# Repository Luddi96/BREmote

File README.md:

# BREmote - Open Source eFoil and Esk8 remote 

## Features:
* All mechanical parts 3D printed (even the springs)
* Symmetric design - left & right side can be swapped
* Sustainable - All external parts can be replaced
* Open Source: 3D Models, Electronics and Software are GPL3.0
* 2.4GHz Link (range dependant on antenna type, position)
* Communication with VESC via UART / CAN
* Low battery alarm (vibration)
* Water ingress alarm integrated in receiver
* Fall-off detection (not yet implemented)
* Gears / Power Levels / Cruise Control
* Charging and Programming via USB

## Links:
* [Promo Video](https://youtu.be/fF5BHrkHTNA)
* [Overview + Build Video](https://youtu.be/kb76z3FXLc0)
* [Updated Build Video](https://youtu.be/RKn8jVGVD6g)
* [Deep Dive Video](https://youtu.be/cdQ3Ppyngpk)
* [Update Video 04/2023](https://youtu.be/SpBOiRbGKgA)
* [Steering & Long Range Update Video](https://youtu.be/DhPk98Wdcn0)

## Parts needed:
### Electronics:
* [Tx & Rx PCBs, order at JLCPCB, Gerbers see releases](https://github.com/Luddi96/BREmote/releases)
	* [Instruction how to order at JLC (only do Step 2&4)](https://youtu.be/y3GviDr0o1s)
* [Tx wireless module "Color: NRF24L01 SMD"](https://de.aliexpress.com/item/1005004905334589.html)
* [Rx wireless module "Color: GT-24 SMD"](https://de.aliexpress.com/item/1005004905334589.html)
* [IPEX Antenna for Rx](https://de.aliexpress.com/item/1005003399563785.html)
* [0.36" 2-digit, 7-Segment Display, Common Cathode "CC"](https://de.aliexpress.com/item/32730115504.html)
* [2x SMD Header, 2x5-pin](https://de.aliexpress.com/item/32336498109.html)
* [EITHER Connector SP13 4-pin](https://de.aliexpress.com/item/1005001891060229.html)
* [OR Magnetic Connector](https://de.aliexpress.com/item/4001283688823.html)
* [Battery Sanyo UR14500AC 740mAh](https://www.nkon.nl/de/sanyo-ur14500ac-740mah-1-52a-reclaimed.html)
* [Vibration Motor 24x7mm, 3.7 to 5V](https://de.aliexpress.com/item/1005004063804397.html)

### Mechanics:
* [2x Magnet N52 D3x6mm](https://www.ebay.de/itm/162903572491?var=461969545239)
* [2x Self-Threading Screw DIN7982 2.2x6.5mm](https://www.ebay.de/itm/272909463518?epid=17007662352)
* [PU Foam, ~Factor 15, e.g. Talamex 45729200](https://www.boatcareshop.nl/bootverf-bootlak/talamex-pu-schuim-2-componenten-200-cc)
* [3D Printed Parts, see releases](https://github.com/Luddi96/BREmote/releases)

## Recommended Connector Pinning:

## Usage:
- With the remote off, push the toggle forward to turn it on
- As long as you keep the toggle forward, you will be shown the internal battery capacity in %
- With `//#define NO_LOCK` disabled in SHARED_CONFIG.h:
	- The remote will start in locked state
	- Push the toggle down to unlock
	- The remote will show you "PP", demanding you to push the trigger to its maximum position
	- Once you release the trigger, the remote will be in operating state
	- Push the toggle up/down to increase/decrease gear (The remote will always start in *lowest* gear)
	- Push and hold the toggle down to lock again
	- Push and hold the toggle up to turn off the remote
- With `#define NO_LOCK` enabled in SHARED_CONFIG.h:
	- The remote will immediately start in unlocked state
	- Push the toggle up/down to increase/decrease gear  (The remote will always start in *highest* gear)
	- Push and hold the toggle up to turn off the remote

## Status Codes:
| Symbol | Meaning |
| --- | --- |
| [] |System Locked |
| PP |Press Trigger once to arm |
| L0-L9 |Current "Gear", use Toggle to change |
| UU |Undervoltage, charge Battery |

## Error Codes:
| Err Code | Meaning | Potential Causes |
| --- | --- | --- |
| E3 | Packet Content Invalid | Unexpected data received, probably due to SW error or signal interference |
| E4 | No Ack | No acknowledgement from Receiver, signal too weak or signal interference |
| E5 | EEPROM Error | Unexpected/no calibration in EEPROM, try calibrating the remote again |
| E6 | NRF Module | NRF (Wireless) Module can't be initialized, probably hardware fault |
| E7 | Water Ingress | Water on the water detection electrodes attached to the receiver. This feature can be disabled in code if you dont use it (default: enabled). |
| E8 | BMS Fault | BMS has disabled its output connected to the receiver. This feature can be disabled in code if you dont use it (default: disabled). |

# Connection Examples:

<details>
<summary>VESC with UART</summary>

</details>

<details>
<summary>ESC or VESC WITHOUT UART</summary>

</details>

<details>
<summary>Steering/Dual Motor</summary>

</details>

---
# FAQ:
Q: When trying to program the remote with the Arduino IDE, I get an error "avrdude: stk500_getsync()"
A: Make sure you selected "Arduino Nano ATmega328P **(Old Bootloader)**"

---
# Changelog:
### 2024-04-15: [Release V1.7]
Note: Changing to this release will require new calibration!
### 2024-04-15: [Source - all]
- Tx:
	- THR_TO_PWRUP: Remote can be set to only turn on when throttle is pressed (more robust to unwanted turn-on)
	- REVERSE: Instead of 10 forward gears, there is a forward and reverse gear 
	- DONT_SEND_IDLE: Remote will stop sending packets when trigger is not pressed (multiple remotes can be used with one Rx, e.g. for sharing a tow boogie)
- Rx:
	- Diff. Steering
- Calibration:
	- Added new paramter for "THR_TO_PWRUP" function
- Add connection example for Steer/Dual Motor
### 2023-12-28: [Release V1.6.4]
### 2023-12-28: [Mechanics - LR]
- Minor changes on main body
	- Longer antenna hole (now 58mm)
	- Reinforcements
### 2023-06-01: [Release V1.6.3]
### 2023-10-02: [Mechanics - LR]
- Added Juergens improved version of the long range bodies
### 2023-06-01: [Release V1.6.2]
### 2023-10-02: [Source - Tx]
- Softer Gears: When at full throttle, changing gear is smoothened (Thanks to Dyse)
### 2023-07-24: [Source - Readme]
- Added Information how to connnect ISP for LR version
### 2023-06-01: [Release V1.6]
### 2023-06-01: [Source]
- Remove Toto Mode
- Add more options to customize UI:
	- NO_LOCK
	- NO_POWERBUTTON
	- NO_GEARS
- Add temperature display
### 2023-05-05: [Release V1.5.1]
### 2023-05-05: [Source - Tx]
- Added "Toto mode" (less filtering for another throttle sensing concept)
- Disable Lock & Poweroff when riding (when throttle is engaged)
### 2023-04-23: [Release V1.5]
### 2023-04-23: [Source]
- Added Steering Function (see [update video](https://youtu.be/DhPk98Wdcn0) )
### 2023-04-23: [Electronics - Tx]
- Added longrange (LR) version of Tx board (uses same NRF module like Rx)
### 2023-04-14: [Release V1.4.2]
### 2023-04-14: [Source]
- Set MOSI Pin to "Input" in standby (Critical fix, as this could damage battery)
### 2023-04-14: [Source]
- Add compiler error if address is not changed
- Increase tolerances on some values
### 2023-04-14: [Release V1.4.1]
### 2023-04-14: [Source - Rx]
- Increased NRF interrupt-to-readout delay
### 2023-03-31: [Release V1.4]
### 2023-03-31: [Readme]
- Added connection diagrams
### 2023-03-31: [Source]
- Made connection to VESC UART optional (defined in SHARED_CONFIG)
- Added analog UBAT measurement
### 2023-03-31: [Electronics - Rx]
- Added component to make analog UBAT measurement more resitant to electromagnetic disturbance
### 2023-03-30: [Source]
- Add error timeout, to allow user to change gear during an error
### 2023-03-12: [Release V1.3]
### 2023-03-20: [Electronics - Rx]
- Added components to make Water Ingress Detection (Wetness Sensor) more resitant to electromagnetic disturbance
### 2023-03-20: [Source]
- Added BMS monitoring function
- Fixed Water Ingress Detection (Wetness Sensor) functionality
### 2023-03-12: [Release V1.2]
### 2023-03-12: [Source]
- Added more information, which Board and Processor to select for programming with Arduino IDE
- Renamed Source Files to not contain Version anymore
- Added Water Ingress Detection (Wetness Sensor) functionality
### 2023-03-07: [Release V1.1]
### 2023-03-04: [Electronics - Tx]
- Made Board 1mm smaller (each 0.5mm from top/bottom)
- Therefore shifted SPI vias and some other traces, changed style of motor pinheaders
### 2023-03-04: [Source]
- Found a error which depleated the battery in standby mode.
- Changed System.ino : disablePower() routine
### 2023-01-20: [Mechanics]
- Added Trigger Opitions with -15 and -30°
- Made Selector Rotator and Selector Spring thinner
- Updated "AllTheSmallThings"
### 2022-12-30: [Mechanics]
- Added Trigger spring with 1mm thickness (before: 1.2mm could lead to spring not being able to "roll in" all the way)
### 2022-12-02: [Electronics - Rx]
- Added protection diode to BMS measurement
### 2022-11-06: [Electronics - Tx]
- Better GND Connection for NRF Module
- Corrected Battery Polarity in whiteprint
- Added Diode to VREF
- Changed Reset to SMD Pad

---
# Credits:
Logo uses "watersport" and "Skate" by Adrien Coquet from https://thenounproject.com/. CC BY 3.0.

Thanks to Daniel for implementing and testing the magnetic connector!
Tanks to Dyse for implementing the soft gears feature!
Thanks to Juergen for the improved long range bodies!

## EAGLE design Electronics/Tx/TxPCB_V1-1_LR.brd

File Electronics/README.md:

## Note:
Before soldering NRF Module in Place, upload Bootloader to Boards. For that, see Source Readme.

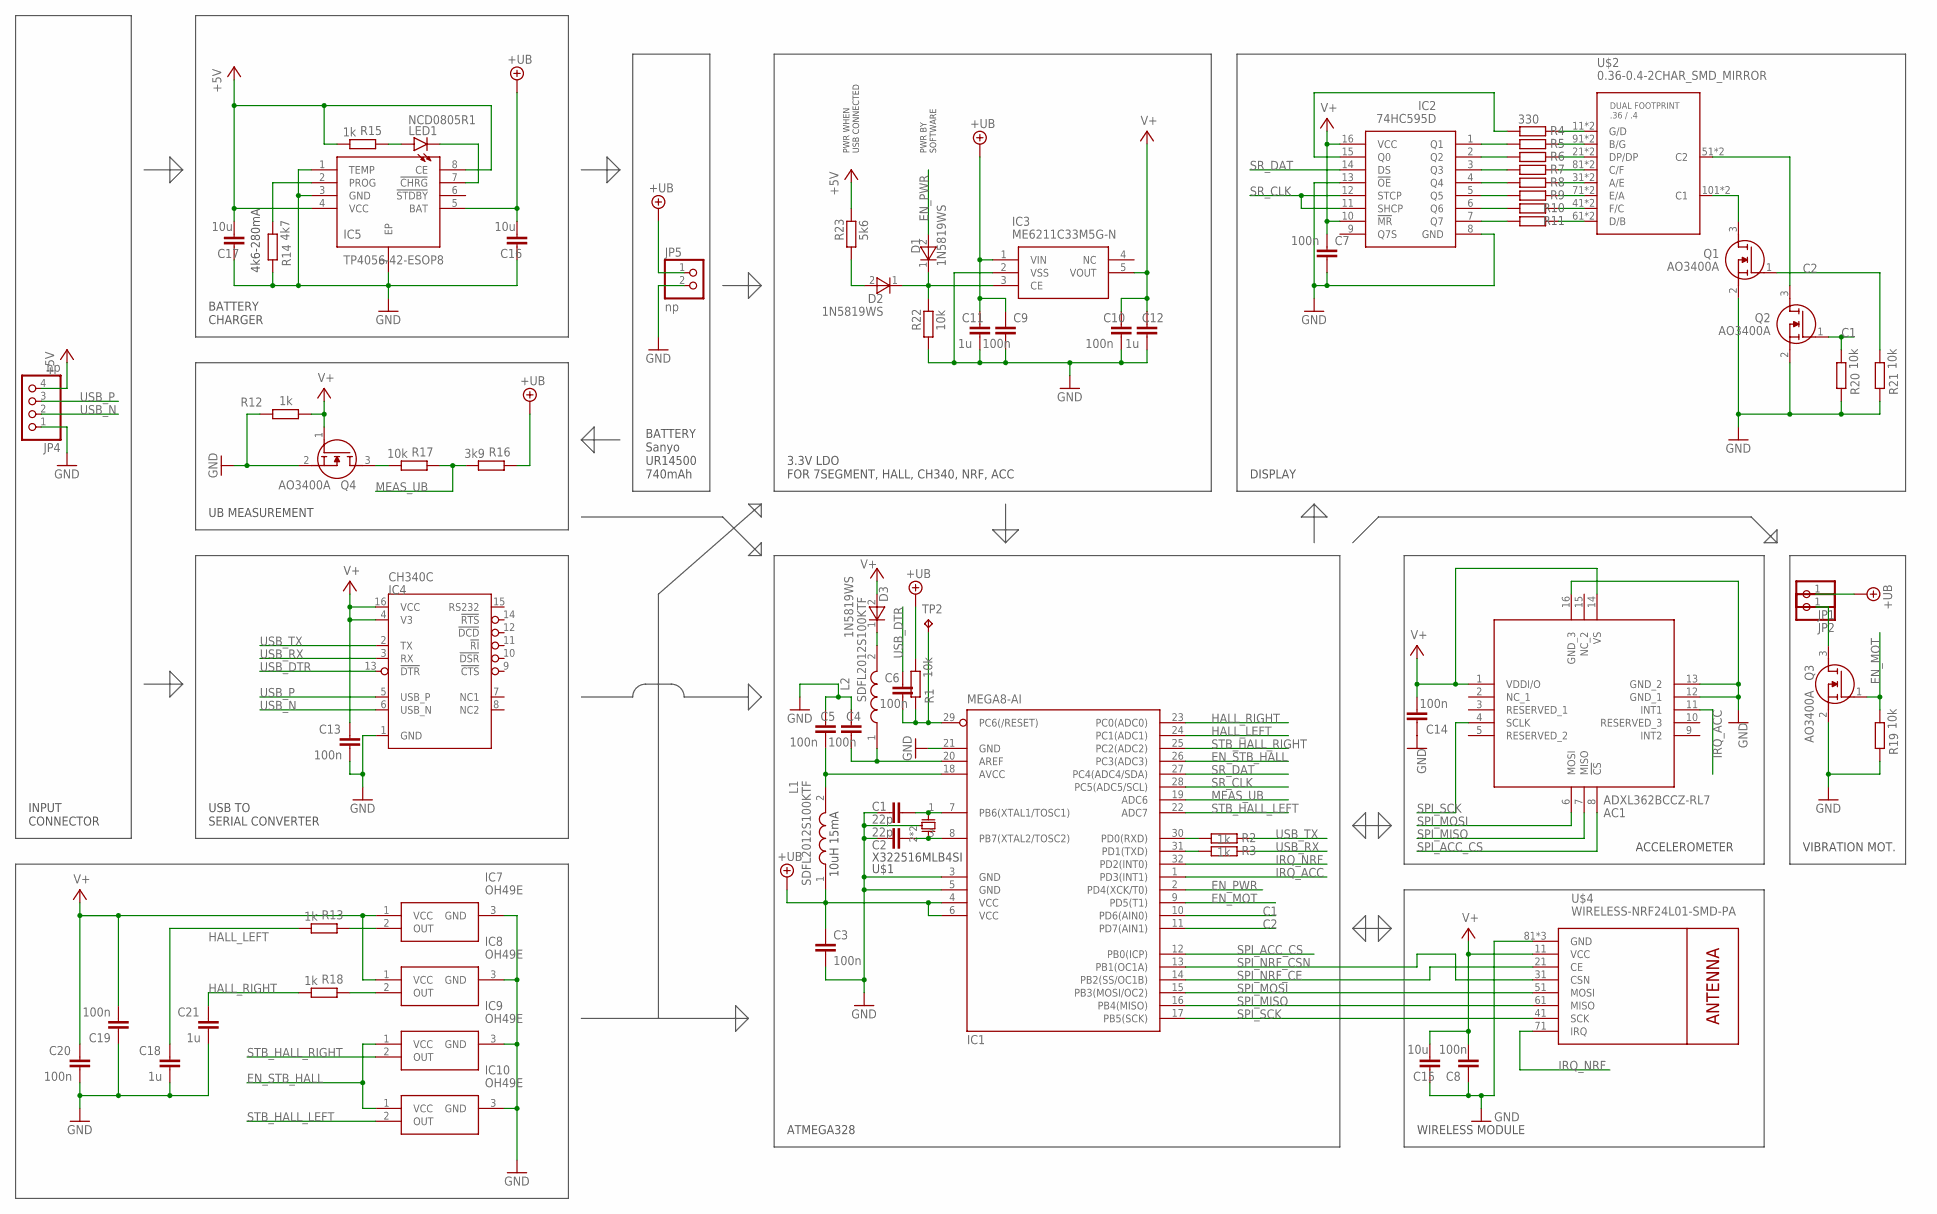
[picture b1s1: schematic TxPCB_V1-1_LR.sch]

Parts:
AC1: ADXL362BCCZ-RL7; CC-16-4
C1, C2: 22p; C0603
C3, C4, C5, C6, C7, C8, C9, C10, C13, C14, C19, C20: 100n; C0603
C11, C12, C18, C21: 1u; C0603
C15, C16, C17: 10u; C0603
D1, D2, D3: 1N5819WS; SODFL2512X90N
IC1: MEGA8-AI; TQFP32-08
IC2: 74HC595D; SOIC127P600X175-16N
IC3: ME6211C33M5G-N; SOT95P282X145-5N
IC4: CH340C; SOIC16N
IC5: TP4056-42-ESOP8; SOIC127P600X175-9N
IC7, IC8, IC9, IC10: OH49E; SOT95P237X112-3N
JP1, JP2: PINHD-1X1; 1X01
JP4: np; 1X04
JP5: np; 1X02
L1, L2: SDFL2012S100KTF; INDC2112X105N
LED1: NCD0805R1; CHIP-LED0805
Q1, Q2, Q3, Q4: AO3400A; SOT95P280X125-3N
R1, R17, R19, R20, R21, R22: 10k; R0603
R2, R3, R12, R13, R15, R18: 1k; R0603
R4, R5, R6, R7, R8, R9, R10, R11: 330; R0603
R14: 4k7; R0603
R16: 3k9; R0603
R23: 5k6; R0603
TP2: TPB1,27; B1,27
U$1: X322516MLB4SI
U$2: 0.36-0.4-2CHAR_SMD_MIRROR; COMBO-036-04_SMD
U$4: WIRELESS-NRF24L01-SMD-PA; WIRELESS-NRF24L01_SMD_PA

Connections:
+5V: C17.1, IC5.4 (VCC), IC5.8 (CE), JP4.4, R15.2, R23.2
+UB: C3.1, C9.1, C11.1, C16.1, IC1.4 (VCC), IC1.6 (VCC), IC3.1 (VIN), IC5.5 (BAT), JP1.1, JP5.1, L1.1, R1.2, R16.1
C1: IC1.10 (PD6(AIN0)), Q2.1 (G), R20.2
C2: IC1.11 (PD7(AIN1)), Q1.1 (G), R21.2
EN_MOT: IC1.9 (PD5(T1)), Q3.1 (G), R19.2
EN_PWR: D1.2 (A), IC1.2 (PD4(XCK/T0))
EN_STB_HALL: IC1.26 (PC3(ADC3)), IC9.1 (VCC), IC10.1 (VCC)
GND: AC1.12 (GND_1), AC1.13 (GND_2), AC1.16 (GND_3), C1.2, C2.2, C3.2, C4.1, C5.1, C7.2, C8.1, C9.2, C10.2, C11.2, C12.2, C13.2, C14.1, C15.2, C16.2, C17.2, C18.2, C19.1, C20.2, C21.2, IC1.3 (GND), IC1.5 (GND), IC1.21 (GND), IC2.8 (GND), IC2.13 (!OE), IC3.2 (VSS), IC4.1 (GND), IC5.1 (TEMP), IC5.3 (GND), IC5.9 (EP), IC7.3 (GND), IC8.3 (GND), IC9.3 (GND), IC10.3 (GND), JP4.1, JP5.2, Q1.2 (S), Q2.2 (S), Q3.2 (S), Q4.2 (S), R12.1, R14.1, R19.1, R20.1, R21.1, R22.1, U$1.2 (G), U$1.4 (G), U$4.81 (GND), U$4.P1 (GND), U$4.P2 (GND)
HALL_LEFT: C18.1, IC1.24 (PC1(ADC1)), R13.2
HALL_RIGHT: C21.1, IC1.23 (PC0(ADC0)), R18.2
IRQ_ACC: AC1.11 (INT1), IC1.1 (PD3(INT1))
IRQ_NRF: IC1.32 (PD2(INT0)), U$4.71 (IRQ)
MEAS_UB: IC1.19 (ADC6), R16.2, R17.1
unnamed: C1.1, IC1.7 (PB6(XTAL1/TOSC1)), U$1.1 (X1)
unnamed: C2.1, IC1.8 (PB7(XTAL2/TOSC2)), U$1.3 (X2)
unnamed: C5.2, IC1.18 (AVCC), L1.2
unnamed: Q4.3 (D), R17.2
unnamed: C6.2, IC1.29 (PC6(/RESET)), R1.1, TP2.TP
unnamed: IC1.30 (PD0(RXD)), R2.2
unnamed: IC1.31 (PD1(TXD)), R3.2
unnamed: R4.1, U$2.11 (G/D), U$2.12 (G/D)
unnamed: R5.1, U$2.91 (B/G), U$2.92 (B/G)
unnamed: R6.1, U$2.21 (DP/DP), U$2.22 (DP/DP)
unnamed: R7.1, U$2.81 (C/F), U$2.82 (C/F)
unnamed: R8.1, U$2.31 (A/E), U$2.32 (A/E)
unnamed: R9.1, U$2.71 (E/A), U$2.72 (E/A)
unnamed: R10.1, U$2.41 (F/C), U$2.42 (F/C)
unnamed: R11.1, U$2.61 (D/B), U$2.62 (D/B)
unnamed: Q1.3 (D), U$2.101 (C1), U$2.102 (C1)
unnamed: Q2.3 (D), U$2.51 (C2), U$2.52 (C2)
unnamed: IC2.1 (Q1), R5.2
unnamed: IC2.2 (Q2), R6.2
unnamed: IC2.3 (Q3), R7.2
unnamed: IC2.4 (Q4), R8.2
unnamed: IC2.5 (Q5), R9.2
unnamed: IC2.6 (Q6), R10.2
unnamed: IC2.7 (Q7), R11.2
unnamed: IC2.15 (Q0), R4.2
unnamed: D2.2 (A), R23.1
unnamed: C4.2, IC1.20 (AREF), L2.1
unnamed: D3.1 (K), L2.2
unnamed: IC8.2 (OUT), R18.1
unnamed: D1.1 (K), D2.1 (K), IC3.3 (CE), R22.2
unnamed: LED1.A, R15.1
unnamed: IC5.7 (!CHRG), LED1.C
unnamed: JP2.1, Q3.3 (D)
unnamed: IC5.2 (PROG), R14.2
unnamed: IC7.2 (OUT), R13.1
SPI_ACC_CS: AC1.8 (!CS), IC1.12 (PB0(ICP))
SPI_MISO: AC1.7 (MISO), IC1.16 (PB4(MISO)), U$4.61 (MISO)
SPI_MOSI: AC1.6 (MOSI), IC1.15 (PB3(MOSI/OC2)), U$4.51 (MOSI)
SPI_NRF_CE: IC1.14 (PB2(SS/OC1B)), U$4.21 (CE)
SPI_NRF_CSN: IC1.13 (PB1(OC1A)), U$4.31 (CSN)
SPI_SCK: AC1.4 (SCLK), IC1.17 (PB5(SCK)), U$4.41 (SCK)
SR_CLK: IC1.28 (PC5(ADC5/SCL)), IC2.11 (SHCP), IC2.12 (STCP)
SR_DAT: IC1.27 (PC4(ADC4/SDA)), IC2.14 (DS)
STB_HALL_LEFT: IC1.22 (ADC7), IC10.2 (OUT)
STB_HALL_RIGHT: IC1.25 (PC2(ADC2)), IC9.2 (OUT)
USB_DTR: C6.1, IC4.13 (!DTR)
USB_N: IC4.6 (USB_N), JP4.2
USB_P: IC4.5 (USB_P), JP4.3
USB_RX: IC4.3 (RX), R3.1
USB_TX: IC4.2 (TX), R2.1
V+: AC1.1 (VDDI/O), AC1.14 (VS), C7.1, C8.2, C10.1, C12.1, C13.1, C14.2, C15.1, C19.2, C20.1, D3.2 (A), IC2.10 (!MR), IC2.16 (VCC), IC3.5 (VOUT), IC4.4 (V3), IC4.16 (VCC), IC7.1 (VCC), IC8.1 (VCC), Q4.1 (G), R12.2, U$4.11 (VCC)

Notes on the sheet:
10uH 15mA
4k6-280mA
INPUT CONNECTOR
USB TO SERIAL CONVERTER
BATTERY CHARGER
UB MEASUREMENT
BATTERY Sanyo UR14500 740mAh
3.3V LDO FOR 7SEGMENT, HALL, CH340, NRF, ACC
ATMEGA328
WIRELESS MODULE
DISPLAY
VIBRATION MOT.
ACCELEROMETER
PWR BY SOFTWARE
PWR WHEN USB CONNECTED

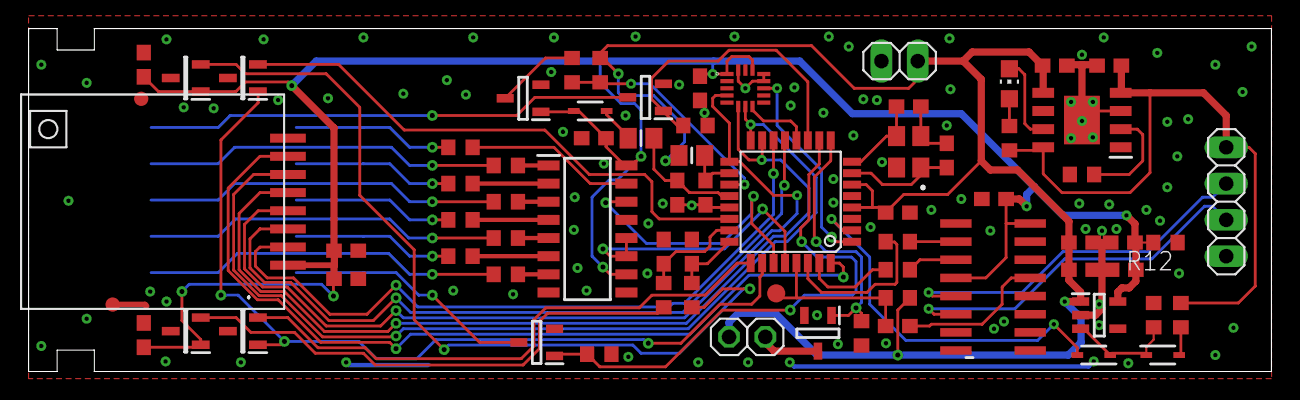
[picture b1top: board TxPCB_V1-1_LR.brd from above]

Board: 2 copper layers, 87.0 x 24.0 mm, 72 parts (1 on the bottom side), 64 nets.

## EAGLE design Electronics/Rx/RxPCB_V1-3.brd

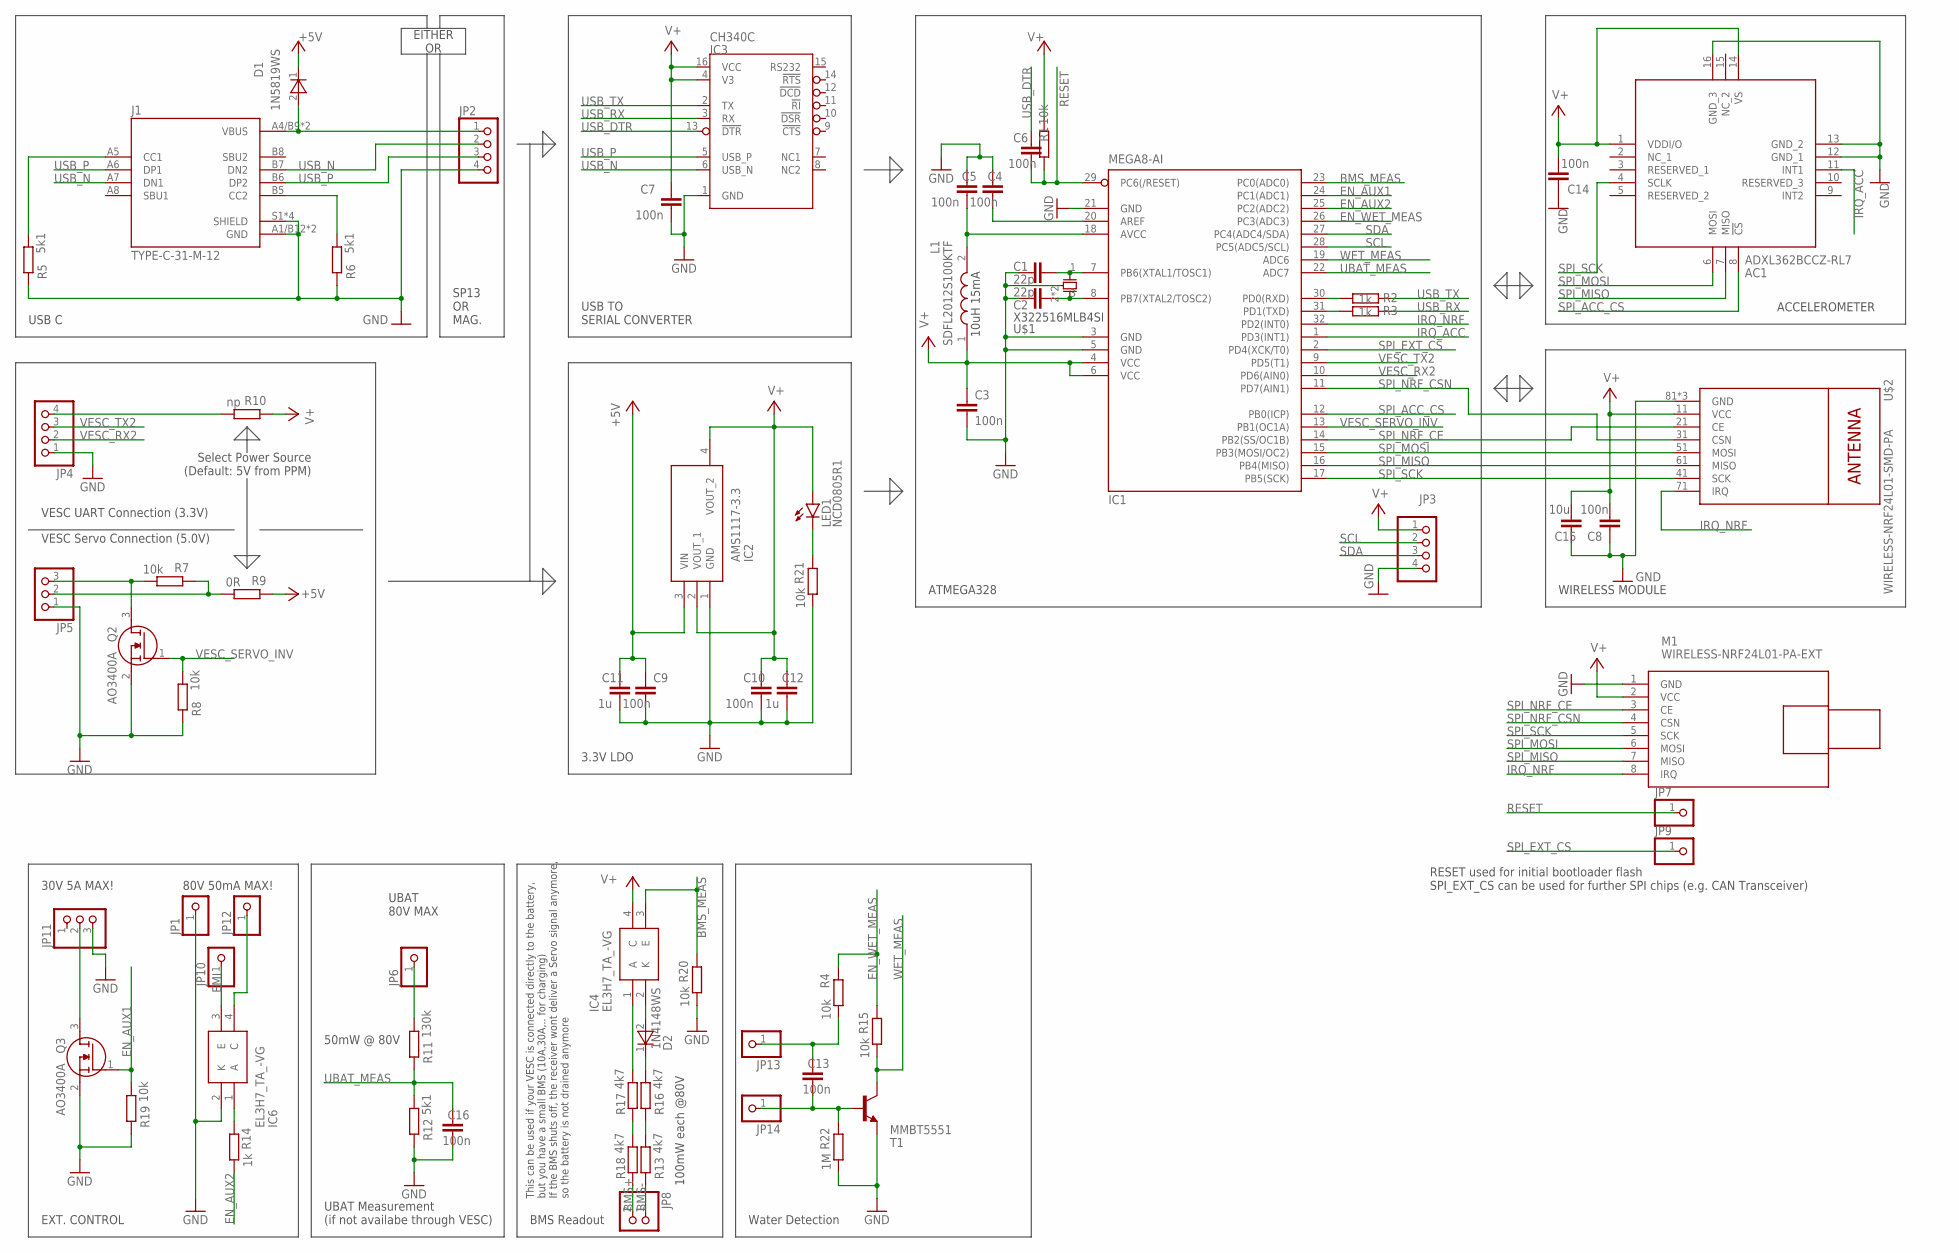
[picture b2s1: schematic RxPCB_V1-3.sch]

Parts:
AC1: ADXL362BCCZ-RL7; CC-16-4
C1, C2: 22p; C0603
C3, C4, C5, C6, C7, C8, C9, C10, C13, C14, C16: 100n; C0603
C11, C12: 1u; C0603
C15: 10u; C0603
D1: 1N5819WS; SODFL2512X90N
D2: 1N4148WS; SODFL2512X90N
IC1: MEGA8-AI; TQFP32-08
IC2: AMS1117-3.3; SOT229P700X180-4N
IC3: CH340C; SOIC16N
IC4, IC6: EL3H7_TA_-VG; SOIC127P700X200-4N
J1: TYPE-C-31-M-12; HRO_TYPE-C-31-M-12
JP1, JP6, JP7, JP9, JP10, JP12, JP13, JP14: PINHD-1X1; 1X01
JP2, JP3, JP4: PINHD-1X4; 1X04
JP5, JP11: PINHD-1X3; 1X03
JP8: PINHD-1X2; 1X02
L1: SDFL2012S100KTF; INDC2112X105N
LED1: NCD0805R1; CHIP-LED0805
M1: WIRELESS-NRF24L01-PA-EXT
Q2, Q3: AO3400A; SOT95P280X125-3N
R1, R4, R7, R8, R15, R19, R20, R21: 10k; R0603
R2, R3, R14: 1k; R0603
R5, R6, R12: 5k1; R0603
R9: 0R; R0603
R10: np; R0603
R11: 130k; R0603
R13, R16, R17, R18: 4k7; R0603
R22: 1M; R0603
T1: MMBT5551; SOT23-BEC
U$1: X322516MLB4SI
U$2: WIRELESS-NRF24L01-SMD-PA; WIRELESS-NRF24L01_SMD_PA

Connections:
+5V: C9.1, C11.1, D1.1 (K), IC2.3 (VIN), R9.1
BMS+: JP8.2, R18.1
BMS-: JP8.1, R13.1
BMS_MEAS: IC1.23 (PC0(ADC0)), IC4.3 (E), R20.1
EMI: IC6.3 (E), JP10.1
EN_AUX1: IC1.24 (PC1(ADC1)), Q3.1 (G), R19.2
EN_AUX2: IC1.25 (PC2(ADC2)), R14.2
EN_WET_MEAS: IC1.26 (PC3(ADC3)), R4.1, R15.1
GND: AC1.12 (GND_1), AC1.13 (GND_2), AC1.16 (GND_3), C1.2, C2.2, C3.2, C4.1, C5.1, C7.2, C8.1, C9.2, C10.2, C11.2, C12.2, C14.1, C15.2, C16.2, IC1.3 (GND), IC1.5 (GND), IC1.21 (GND), IC2.1 (GND), IC3.1 (GND), IC6.2 (K), J1.A1/B12 (GND), J1.B1/A12 (GND), J1.S1 (SHIELD), J1.S2 (SHIELD), J1.S3 (SHIELD), J1.S4 (SHIELD), JP1.1, JP2.4, JP3.4, JP4.1, JP5.1, JP11.3, M1.1 (GND), Q2.2 (S), Q3.2 (S), R5.1, R6.1, R8.1, R12.1, R19.1, R20.2, R21.2, R22.2, T1.E, U$1.2 (G), U$1.4 (G), U$2.81 (GND), U$2.P1 (GND), U$2.P2 (GND)
IRQ_ACC: AC1.11 (INT1), IC1.1 (PD3(INT1))
IRQ_NRF: IC1.32 (PD2(INT0)), M1.8 (IRQ), U$2.71 (IRQ)
unnamed: C1.1, IC1.7 (PB6(XTAL1/TOSC1)), U$1.1 (X1)
unnamed: C2.1, IC1.8 (PB7(XTAL2/TOSC2)), U$1.3 (X2)
unnamed: C5.2, IC1.18 (AVCC), L1.2
unnamed: J1.A5 (CC1), R5.2
unnamed: IC4.1 (A), R17.2
unnamed: IC1.30 (PD0(RXD)), R2.2
unnamed: IC1.31 (PD1(TXD)), R3.2
unnamed: D1.2 (A), J1.A4/B9 (VBUS), J1.B4/A9 (VBUS), JP2.1
unnamed: LED1.C, R21.1
unnamed: J1.B5 (CC2), R6.2
unnamed: IC6.4 (C), JP12.1
unnamed: JP4.4, R10.2
unnamed: JP5.2, R7.1, R9.2
unnamed: D2.1 (K), R16.2
unnamed: JP6.1, R11.2
unnamed: D2.2 (A), IC4.2 (K)
unnamed: C13.2, JP14.1, R22.1, T1.B
unnamed: C13.1, JP13.1, R4.2
unnamed: IC6.1 (A), R14.1
unnamed: R13.2, R16.1
unnamed: R17.1, R18.2
unnamed: C4.2, IC1.20 (AREF)
unnamed: JP11.2, Q3.3 (D)
RESET: C6.2, IC1.29 (PC6(/RESET)), JP7.1, R1.1
SCL: IC1.28 (PC5(ADC5/SCL)), JP3.2
SDA: IC1.27 (PC4(ADC4/SDA)), JP3.3
SPI_ACC_CS: AC1.8 (!CS), IC1.12 (PB0(ICP))
SPI_EXT_CS: IC1.2 (PD4(XCK/T0)), JP9.1
SPI_MISO: AC1.7 (MISO), IC1.16 (PB4(MISO)), M1.7 (MISO), U$2.61 (MISO)
SPI_MOSI: AC1.6 (MOSI), IC1.15 (PB3(MOSI/OC2)), M1.6 (MOSI), U$2.51 (MOSI)
SPI_NRF_CE: IC1.14 (PB2(SS/OC1B)), M1.3 (CE), U$2.21 (CE)
SPI_NRF_CSN: IC1.11 (PD7(AIN1)), M1.4 (CSN), U$2.31 (CSN)
SPI_SCK: AC1.4 (SCLK), IC1.17 (PB5(SCK)), M1.5 (SCK), U$2.41 (SCK)
UBAT_MEAS: C16.1, IC1.22 (ADC7), R11.1, R12.2
USB_DTR: C6.1, IC3.13 (!DTR)
USB_N: IC3.6 (USB_N), J1.A7 (DN1), J1.B7 (DN2), JP2.2
USB_P: IC3.5 (USB_P), J1.A6 (DP1), J1.B6 (DP2), JP2.3
USB_RX: IC3.3 (RX), R3.1
USB_TX: IC3.2 (TX), R2.1
V+: AC1.1 (VDDI/O), AC1.14 (VS), C3.1, C7.1, C8.2, C10.1, C12.1, C14.2, C15.1, IC1.4 (VCC), IC1.6 (VCC), IC2.2 (VOUT_1), IC2.4 (VOUT_2), IC3.4 (V3), IC3.16 (VCC), IC4.4 (C), JP3.1, L1.1, LED1.A, M1.2 (VCC), R1.2, R10.1, U$2.11 (VCC)
VESC_RX2: IC1.10 (PD6(AIN0)), JP4.2
VESC_SERVO_5V: JP5.3, Q2.3 (D), R7.2
VESC_SERVO_INV: IC1.13 (PB1(OC1A)), Q2.1 (G), R8.2
VESC_TX2: IC1.9 (PD5(T1)), JP4.3
WET_MEAS: IC1.19 (ADC6), R15.2, T1.C

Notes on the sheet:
10uH 15mA
USB C
3.3V LDO
ATMEGA328
WIRELESS MODULE
EXT. CONTROL
ACCELEROMETER
USB TO SERIAL CONVERTER
SP13 OR MAG.
EITHER OR
VESC UART Connection (3.3V)
VESC Servo Connection (5.0V)
Select Power Source (Default: 5V from PPM)
UBAT 80V MAX
50mW @ 80V
UBAT Measurement (if not availabe through VESC)
30V 5A MAX!
80V 50mA MAX!
Water Detection
RESET used for initial bootloader flash SPI_EXT_CS can be used for further SPI chips (e.g. CAN Transceiver)
BMS Readout
100mW each @80V
This can be used if your VESC is connected directly to the battery, but you have a small BMS (10A,30A,.. for charging) If the BMS shuts off, the receiver wont deliver a Servo signal anymore, so the battery is not drained anymore

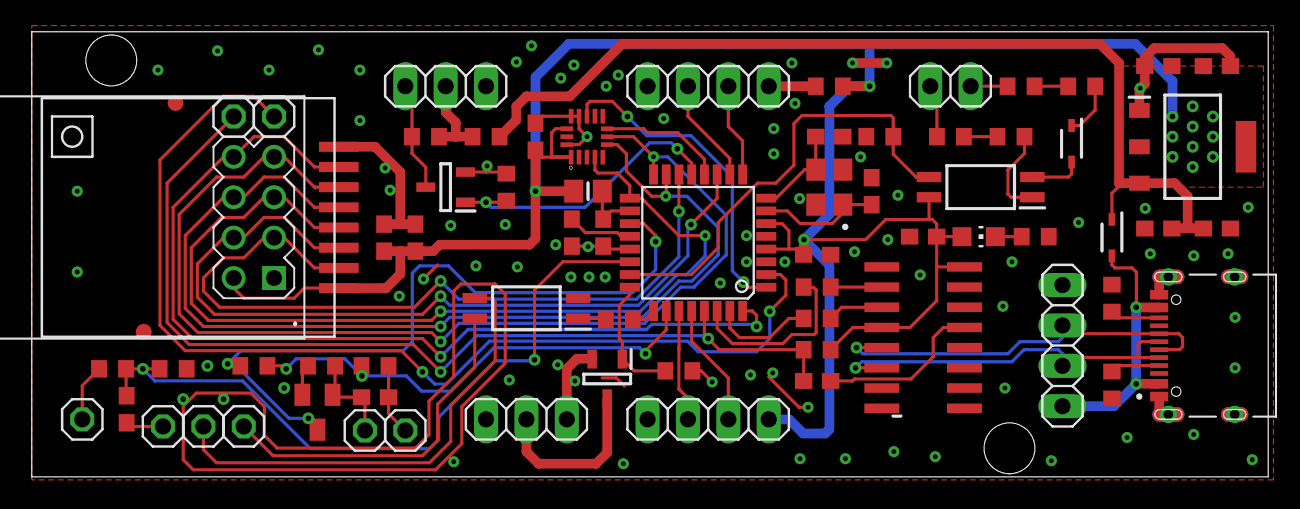
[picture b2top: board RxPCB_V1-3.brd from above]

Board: 2 copper layers, 77.8 x 28.0 mm, 69 parts (0 on the bottom side), 56 nets.

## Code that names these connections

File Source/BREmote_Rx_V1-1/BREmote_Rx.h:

/*
    BREmote V1.1
    Copyright (C) 2022 Ludwig Brechter (contact@lbre.de)
    
    This program is free software: you can redistribute it and/or modify
    it under the terms of the GNU General Public License as published by
    the Free Software Foundation, either version 3 of the License, or
    (at your option) any later version.
    
    This program is distributed in the hope that it will be useful,
    but WITHOUT ANY WARRANTY; without even the implied warranty of
    MERCHANTABILITY or FITNESS FOR A PARTICULAR PURPOSE.  See the
    GNU General Public License for more details.
    
    You should have received a copy of the GNU General Public License
    along with this program.  If not, see <http://www.gnu.org/licenses/>.
 */

/*
 * Includes
 */
 #include "SHARED_CONFIG.h"
#include <SPI.h>
#include <nRF24L01.h>
#include <RF24.h>
#include <SoftwareSerial.h>

#include "datatypes.h"
#include "buffer.h"
#include "crc.h"


/*
 * Variables
 */

// 0: Check to Remote, 1: Special Code, 2: Battery VESC, 3: 0xFF
volatile uint8_t payload_arr[] = {0x0B, 0x00, 99, 0xFF};
// 0: Check from Remote, 1: Trigger value, 2: 0xFF
volatile uint8_t rx_arr[3];
volatile uint8_t last_check = payload_arr[0];

volatile unsigned long last_packet = 0;
volatile uint8_t thr_received = 0;

volatile int16_t fetTemp = 0;
volatile int32_t motCur = 0;
volatile int32_t batCur = 0;
volatile int16_t duty = 0;
volatile int16_t batVolt = VESC_BAT_FULL_AT;

volatile bool failsafe = 1;

//#define VESC_MORE_VALUES

#ifdef VESC_MORE_VALUES
  #define VESC_PACK_LEN 19
  uint8_t vescRelayBuffer[25];
#else
  #define VESC_PACK_LEN 9
  uint8_t vescRelayBuffer[15];
#endif

//#define VESC_RELAY_MODE

#ifdef VESC_RELAY_MODE
  uint8_t txdiv = 0;
  uint8_t relayAddr[6] = {"BREAR"};
#endif


#define PWM_INVERTED

/*
 * Defines
 */

//Analog
#define BMS_MEAS A0
#define EN_AUX1 A1
#define EN_AUX2 A2
#define EN_WET_MEAS A3
#define SDA A4
#define SCL A5
#define WET_MEAS A6
#define UBAT_MEAS A7

//SPI (NRF & ACC)
#define SPI_MOSI 11
#define SPI_MISO 12
#define SPI_SCK 13

#define NRF_CE 10
#define NRF_CSN 7
#define NRF_IRQ 2

#define ACC_CS 8
#define ACC_IRQ 3

#define EXT_CS 4

//UART2 to VESC
#define VESC_TX2 5
#define VESC_RX2 6

//Servo
#define VESC_SERVO_INV 9 //This must be Pin 9 or 10

/*
 * Debug
 */
#ifdef DEBUG
#define DEBUG_PRINT(x) Serial.print(x)
#define DEBUG_PRINTLN(x) Serial.println(x)
#else
#define DEBUG_PRINT(x)
#define DEBUG_PRINTLN(x)
#endif

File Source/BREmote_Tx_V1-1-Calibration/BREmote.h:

/*
    BREmote V1.1
    Copyright (C) 2022 Ludwig Brechter (contact@lbre.de)
    
    This program is free software: you can redistribute it and/or modify
    it under the terms of the GNU General Public License as published by
    the Free Software Foundation, either version 3 of the License, or
    (at your option) any later version.
    
    This program is distributed in the hope that it will be useful,
    but WITHOUT ANY WARRANTY; without even the implied warranty of
    MERCHANTABILITY or FITNESS FOR A PARTICULAR PURPOSE.  See the
    GNU General Public License for more details.
    
    You should have received a copy of the GNU General Public License
    along with this program.  If not, see <http://www.gnu.org/licenses/>.
 */

#define DEBUG

/*
 * Variables
 */
volatile bool power_enabled = 0;
 
int16_t meas_A0 = 0;
int16_t meas_A1 = 0;
int16_t meas_A2 = 0;
int16_t meas_A7 = 0;

/*
 * Includes
 */

#include <SPI.h>
#include <nRF24L01.h>
#include <RF24.h>
#include <EEPROM.h>

/*
 * Defines
 */

#define EE_VAL_FLAG 3
#define EE_LEFTHANDER 4
#define EE_THR_MIN 5
#define EE_THR_MAX 7
#define EE_THR_REV 9
#define EE_TOG     10
#define EE_TOG_STB 12
#define EE_TOG_REV 14

//Display:
#define SR_DAT A4
#define SR_CLK A5
#define C1 7 //Changed here
#define C2 6 //Changed here

//SPI (NRF & ACC)
#define SPI_MOSI 11
#define SPI_MISO 12
#define SPI_SCK 13

#define NRF_CE 10
#define NRF_CSN 9
#define NRF_IRQ 2 

#define ACC_CS 8
#define ACC_IRQ 3

#define HALL_EN A3

//MISC
#define MEAS_UB A6
#define EN_PWR 4
#define EN_MOT 5

/*
 * Debug
 */
#ifdef DEBUG
#define DEBUG_PRINT(x) Serial.print(x)
#define DEBUG_PRINTLN(x) Serial.println(x)
#else
#define DEBUG_PRINT(x)
#define DEBUG_PRINTLN(x)
#endif

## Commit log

2023-03-07 Add issue templates
2023-03-07 Cleanup README.md
2023-03-12 Implement Wetness Sensor Function
    Also renamed folders and file names
    to not contain version number anymore.
2023-03-20 Add BMS Monitoring, Fix Wetness Sensor
    - Added BMS Monitoring in Source
    - Fixed Wetness Sensor (EMI resiliance)
2023-03-29 Add timeout to error display
    In order to allow the user to change gear during an error, a timeout is introduced.
2023-03-29 Add Bootloader flashing instruciton to Source Readme
2023-03-31 Add analog UBAT meas and add connection info to Readme
    [Readme]
    - Added connection diagrams
    [Source]
    - Made connection to VESC UART optional (defined in SHARED_CONFIG)
    - Added analog UBAT measurement
    [Electronics - Rx]
2023-04-14 Add Mfg. Test Programms
2023-04-14 Increase NRF interrupt-to-readout delay
2023-04-20 Add compiler error if address is not changed, increase tolerances on some values
2023-04-20 Important fix: Disable MOSI Pin (could damage battery in standby)
2023-04-23 Add longrange (LR) and steering functionality
    Add a longrange (LR) version of Tx board
    Add steering functionality in code
2023-05-05 Add "TOTO-Mode", Disable Lock&Poweroff when Throttle is active
2023-06-01 UI Overhaul
    Remove Toto Mode
    Add more options to customize UI:
    - NO_LOCK
    - NO_POWERBUTTON
    - NO_GEARS
    Add temperature display
2023-06-03 Put "last_activity check" into defines
2023-10-02 Add softer gears
    - Softer Gears: When at full throttle, changing gear is smoothened (Thanks to Dyse)
    - Added Information how to connnect ISP for LR version
2023-10-17 Add improved LR bodies
2023-12-28 Update of LR main body housing
    - Longer antenna hole (now 58mm)
    - Reinforcements
2024-04-15 Release V1.7
    Note: Changing to this release will require new calibration!

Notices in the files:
parts and their libraries:
diy-modules: Released under the Creative Commons Attribution 4.0 International License: http://creativecommons.org/licenses/by/4.0
